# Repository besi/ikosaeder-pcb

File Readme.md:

# [Ikosaeder PCB][1]

![Screenshot][]

[1]: https://github.com/besi/ikosaeder-pcb
[screenshot]: https://github.com/besi/ikosaeder-pcb/raw/master/screenshot.png

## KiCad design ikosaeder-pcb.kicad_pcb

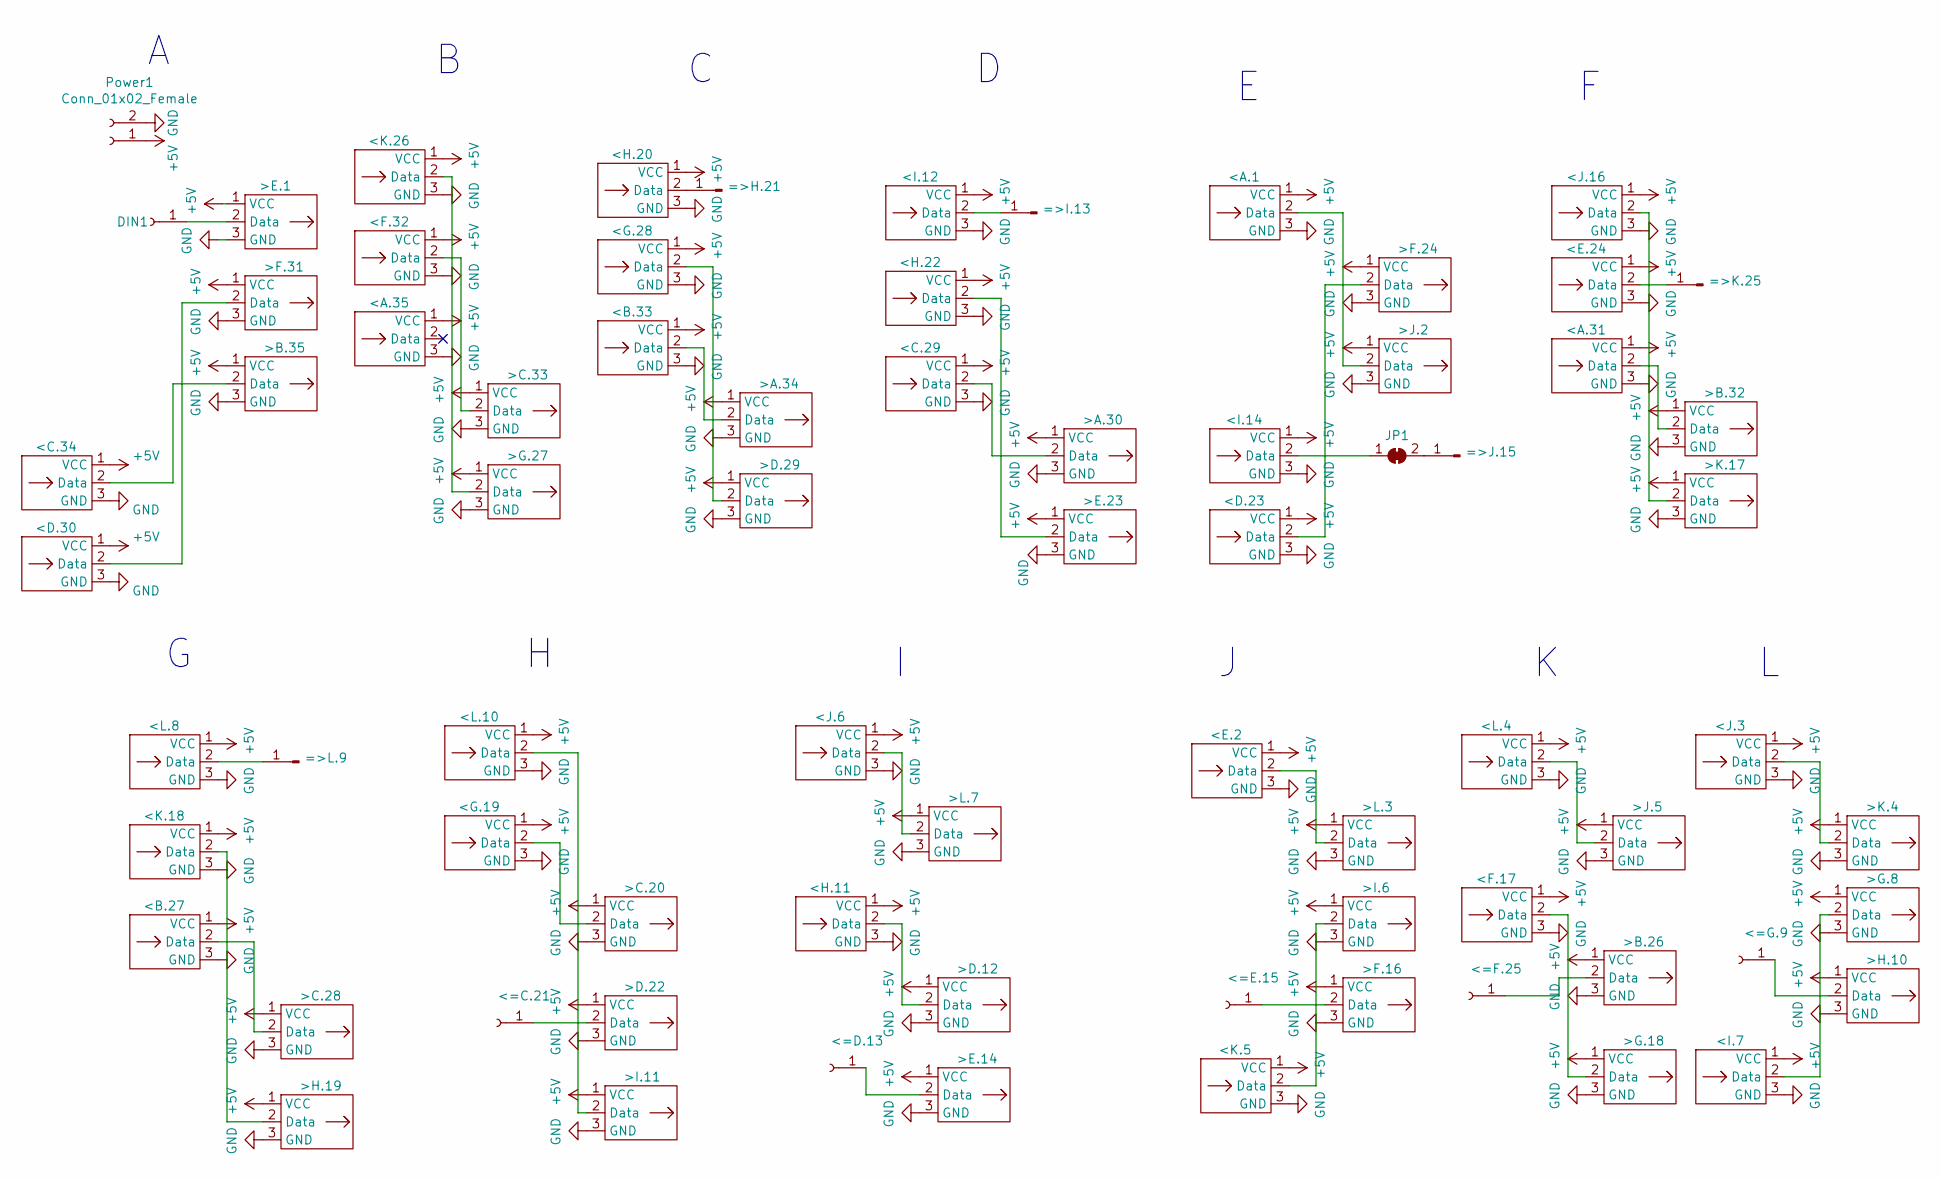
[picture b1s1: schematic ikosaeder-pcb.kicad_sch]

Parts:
<=C.21: Conn_01x01_Female; PinHeader_1x01_P2.54mm_Vertical
<=D.13: Conn_01x01_Female; PinHeader_1x01_P2.54mm_Vertical
<=E.15: Conn_01x01_Female; PinHeader_1x01_P2.54mm_Vertical
<=F.25: Conn_01x01_Female; PinHeader_1x01_P2.54mm_Vertical
<=G.9: Conn_01x01_Female; PinHeader_1x01_P2.54mm_Vertical
<A.1, <A.31, <A.35: LEDs_In; LED-Strip
<B.27, <B.33: LEDs_In; LED-Strip
<C.29, <C.34: LEDs_In; LED-Strip
<D.23, <D.30: LEDs_In; LED-Strip
<E.2, <E.24: LEDs_In; LED-Strip
<F.17, <F.32: LEDs_In; LED-Strip
<G.19, <G.28: LEDs_In; LED-Strip
<H.11, <H.20, <H.22: LEDs_In; LED-Strip
<I.7, <I.12, <I.14: LEDs_In; LED-Strip
<J.3, <J.6, <J.16: LEDs_In; LED-Strip
<K.5, <K.18, <K.26: LEDs_In; LED-Strip
<L.4, <L.8, <L.10: LEDs_In; LED-Strip
=>H.21: Conn_01x01_Male; PinHeader_1x01_P2.54mm_Vertical
=>I.13: Conn_01x01_Male; PinHeader_1x01_P2.54mm_Vertical
=>J.15: Conn_01x01_Male; PinHeader_1x01_P2.54mm_Vertical
=>K.25: Conn_01x01_Male; PinHeader_1x01_P2.54mm_Vertical
=>L.9: Conn_01x01_Male; PinHeader_1x01_P2.54mm_Vertical
>A.30, >A.34: LEDs_Out; LED-Strip
>B.26, >B.32, >B.35: LEDs_Out; LED-Strip
>C.20, >C.28, >C.33: LEDs_Out; LED-Strip
>D.12, >D.22, >D.29: LEDs_Out; LED-Strip
>E.1, >E.14, >E.23: LEDs_Out; LED-Strip
>F.16, >F.24, >F.31: LEDs_Out; LED-Strip
>G.8, >G.18, >G.27: LEDs_Out; LED-Strip
>H.10, >H.19: LEDs_Out; LED-Strip
>I.6, >I.11: LEDs_Out; LED-Strip
>J.2, >J.5: LEDs_Out; LED-Strip
>K.4, >K.17: LEDs_Out; LED-Strip
>L.3, >L.7: LEDs_Out; LED-Strip
DIN1: Conn_01x01_Female; PinHeader_1x01_P2.54mm_Vertical
JP1: SolderJumper_2_Bridged; SolderJumper-2_P1.3mm_Bridged_RoundedPad1.0x1.5mm
Power1: Conn_01x02_Female; PinHeader_1x02_P2.54mm_Vertical

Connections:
+5V: <A.1.1 (VCC), <A.31.1 (VCC), <A.35.1 (VCC), <B.27.1 (VCC), <B.33.1 (VCC), <C.29.1 (VCC), <C.34.1 (VCC), <D.23.1 (VCC), <D.30.1 (VCC), <E.2.1 (VCC), <E.24.1 (VCC), <F.17.1 (VCC), <F.32.1 (VCC), <G.19.1 (VCC), <G.28.1 (VCC), <H.11.1 (VCC), <H.20.1 (VCC), <H.22.1 (VCC), <I.7.1 (VCC), <I.12.1 (VCC), <I.14.1 (VCC), <J.3.1 (VCC), <J.6.1 (VCC), <J.16.1 (VCC), <K.5.1 (VCC), <K.18.1 (VCC), <K.26.1 (VCC), <L.4.1 (VCC), <L.8.1 (VCC), <L.10.1 (VCC), >A.30.1 (VCC), >A.34.1 (VCC), >B.26.1 (VCC), >B.32.1 (VCC), >B.35.1 (VCC), >C.20.1 (VCC), >C.28.1 (VCC), >C.33.1 (VCC), >D.12.1 (VCC), >D.22.1 (VCC), >D.29.1 (VCC), >E.1.1 (VCC), >E.14.1 (VCC), >E.23.1 (VCC), >F.16.1 (VCC), >F.24.1 (VCC), >F.31.1 (VCC), >G.8.1 (VCC), >G.18.1 (VCC), >G.27.1 (VCC), >H.10.1 (VCC), >H.19.1 (VCC), >I.6.1 (VCC), >I.11.1 (VCC), >J.2.1 (VCC), >J.5.1 (VCC), >K.4.1 (VCC), >K.17.1 (VCC), >L.3.1 (VCC), >L.7.1 (VCC), Power1.1
GND: <A.1.3 (GND), <A.31.3 (GND), <A.35.3 (GND), <B.27.3 (GND), <B.33.3 (GND), <C.29.3 (GND), <C.34.3 (GND), <D.23.3 (GND), <D.30.3 (GND), <E.2.3 (GND), <E.24.3 (GND), <F.17.3 (GND), <F.32.3 (GND), <G.19.3 (GND), <G.28.3 (GND), <H.11.3 (GND), <H.20.3 (GND), <H.22.3 (GND), <I.7.3 (GND), <I.12.3 (GND), <I.14.3 (GND), <J.3.3 (GND), <J.6.3 (GND), <J.16.3 (GND), <K.5.3 (GND), <K.18.3 (GND), <K.26.3 (GND), <L.4.3 (GND), <L.8.3 (GND), <L.10.3 (GND), >A.30.3 (GND), >A.34.3 (GND), >B.26.3 (GND), >B.32.3 (GND), >B.35.3 (GND), >C.20.3 (GND), >C.28.3 (GND), >C.33.3 (GND), >D.12.3 (GND), >D.22.3 (GND), >D.29.3 (GND), >E.1.3 (GND), >E.14.3 (GND), >E.23.3 (GND), >F.16.3 (GND), >F.24.3 (GND), >F.31.3 (GND), >G.8.3 (GND), >G.18.3 (GND), >G.27.3 (GND), >H.10.3 (GND), >H.19.3 (GND), >I.6.3 (GND), >I.11.3 (GND), >J.2.3 (GND), >J.5.3 (GND), >K.4.3 (GND), >K.17.3 (GND), >L.3.3 (GND), >L.7.3 (GND), Power1.2
unnamed: <=C.21.1, >D.22.2 (Data)
unnamed: <=D.13.1, >E.14.2 (Data)
unnamed: <=E.15.1, >F.16.2 (Data)
unnamed: <=F.25.1, >B.26.2 (Data)
unnamed: <=G.9.1, >H.10.2 (Data)
unnamed: <A.1.2 (Data), >J.2.2 (Data)
unnamed: <A.31.2 (Data), >B.32.2 (Data)
unnamed: <B.27.2 (Data), >C.28.2 (Data)
unnamed: <B.33.2 (Data), >A.34.2 (Data)
unnamed: <C.29.2 (Data), >A.30.2 (Data)
unnamed: <C.34.2 (Data), >B.35.2 (Data)
unnamed: <D.23.2 (Data), >F.24.2 (Data)
unnamed: <D.30.2 (Data), >F.31.2 (Data)
unnamed: <E.2.2 (Data), >L.3.2 (Data)
unnamed: <E.24.2 (Data), =>K.25.1
unnamed: <F.17.2 (Data), >G.18.2 (Data)
unnamed: <F.32.2 (Data), >C.33.2 (Data)
unnamed: <G.19.2 (Data), >C.20.2 (Data)
unnamed: <G.28.2 (Data), >D.29.2 (Data)
unnamed: <H.11.2 (Data), >D.12.2 (Data)
unnamed: <H.20.2 (Data), =>H.21.1
unnamed: <H.22.2 (Data), >E.23.2 (Data)
unnamed: <I.7.2 (Data), >G.8.2 (Data)
unnamed: <I.12.2 (Data), =>I.13.1
unnamed: <I.14.2 (Data), JP1.1 (A)
unnamed: <J.3.2 (Data), >K.4.2 (Data)
unnamed: <J.6.2 (Data), >L.7.2 (Data)
unnamed: <J.16.2 (Data), >K.17.2 (Data)
unnamed: <K.5.2 (Data), >I.6.2 (Data)
unnamed: <K.18.2 (Data), >H.19.2 (Data)
unnamed: <K.26.2 (Data), >G.27.2 (Data)
unnamed: <L.4.2 (Data), >J.5.2 (Data)
unnamed: <L.8.2 (Data), =>L.9.1
unnamed: <L.10.2 (Data), >I.11.2 (Data)
unnamed: =>J.15.1, JP1.2 (B)
unnamed: >E.1.2 (Data), DIN1.1

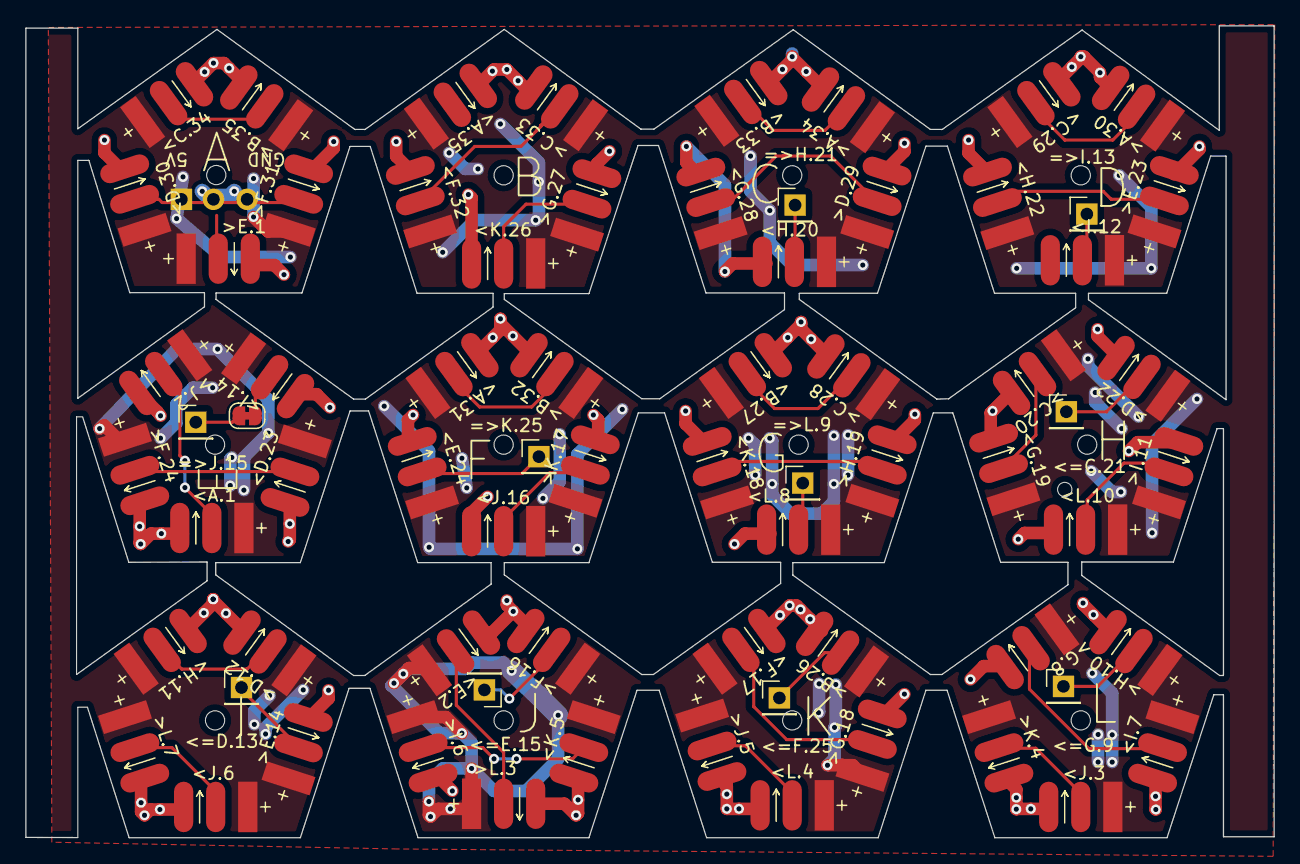
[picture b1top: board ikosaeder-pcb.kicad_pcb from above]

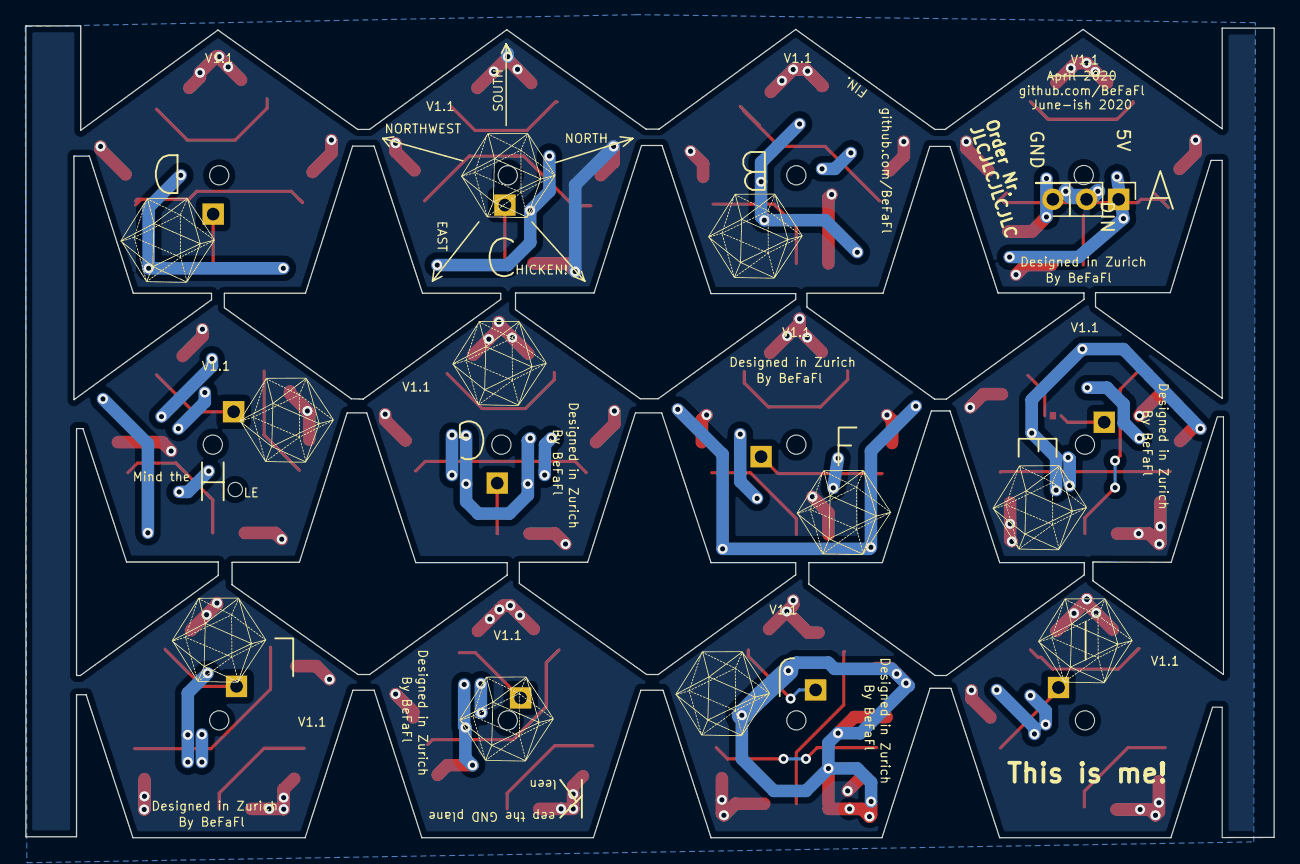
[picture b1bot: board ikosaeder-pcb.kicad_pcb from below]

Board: 2 copper layers, 98.9 x 64.3 mm, 73 parts (2 on the bottom side), 38 nets.

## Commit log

2020-04-06 Pentagram shaped pcb
2020-04-06 Move information to the comments layer
2020-04-06 Add GND/ 5V and standard headers
2020-04-07 Make the first pcb board which has the label A
2020-04-07 Add the screenshot to the readme
2020-04-08 Minor tweaks
    - Add male / female connector for semantic purposes
    - Consolidate the connectors
    - Prepare for 12 pcbs
    - Use clockwise arrangement
2020-06-13 Ikosaeder final
2020-06-21 Add Logo
2021-04-11 Fix errors
2021-12-27 Update pcb
2026-01-08 Add project and .gitignore to VCS
